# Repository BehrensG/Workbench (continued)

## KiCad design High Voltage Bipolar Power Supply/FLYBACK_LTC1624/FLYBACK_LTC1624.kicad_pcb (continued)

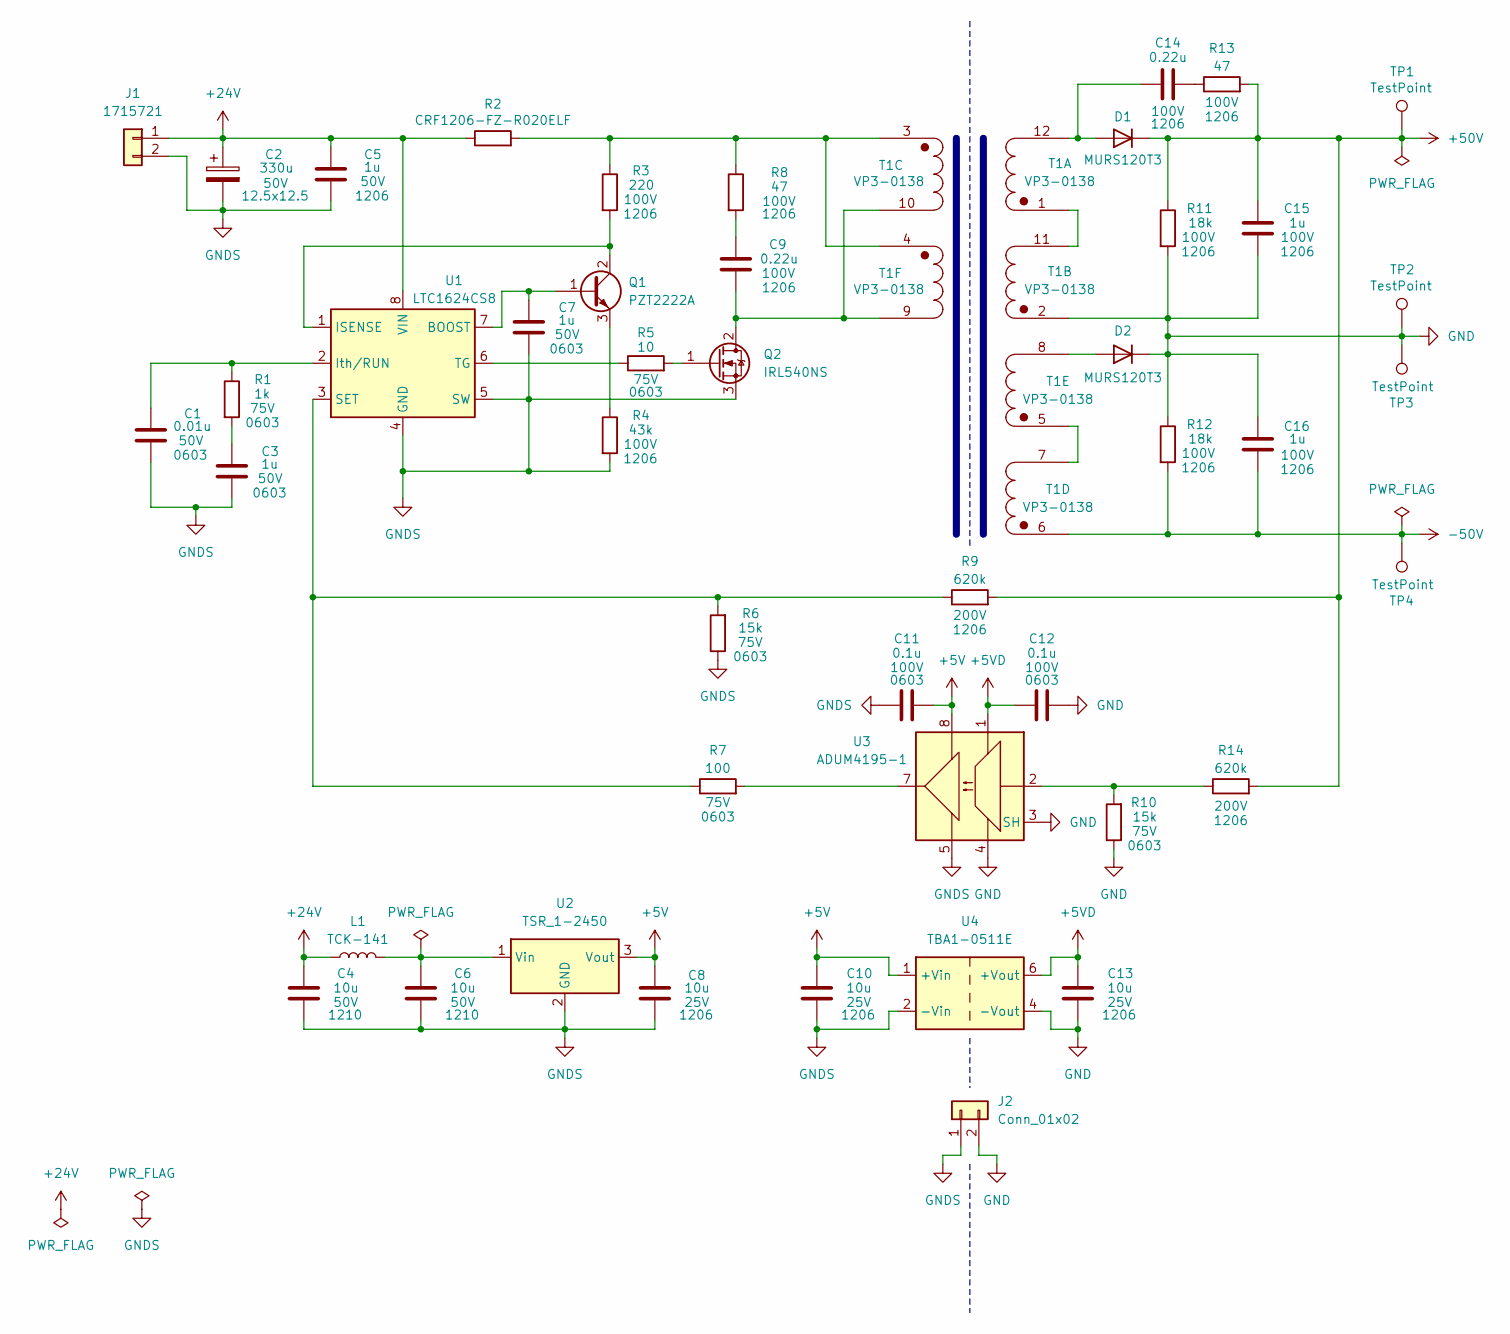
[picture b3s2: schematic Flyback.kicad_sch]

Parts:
C1: 0.01u; C_0603_1608Metric_Pad1.08x0.95mm_HandSolder; Voltage 50V
C2: 330u; CP_Elec_10x10; Voltage 50V
C3, C7: 1u; C_0603_1608Metric_Pad1.08x0.95mm_HandSolder; Voltage 50V
C4, C6: 10u; C_1210_3225Metric_Pad1.33x2.70mm_HandSolder; Voltage 50V
C5: 1u; C_1206_3216Metric_Pad1.33x1.80mm_HandSolder; Voltage 50V
C8, C10, C13: 10u; C_1206_3216Metric_Pad1.33x1.80mm_HandSolder; Voltage 25V
C9, C14: 0.22u; C_1206_3216Metric_Pad1.33x1.80mm_HandSolder; Voltage 100V
C11, C12: 0.1u; C_0603_1608Metric_Pad1.08x0.95mm_HandSolder; Voltage 100V
C15, C16: 1u; C_1206_3216Metric_Pad1.33x1.80mm_HandSolder; Voltage 100V
D1, D2: MURS120T3; D_SMB
J1: 1715721; TerminalBlock_Phoenix_MKDS-1,5-2_1x02_P5.00mm_Horizontal
J2: Conn_01x02; PinHeader_1x02_P2.54mm_Vertical
L1: TCK-141
Q1: PZT2222A; SOT-223-3_TabPin2
Q2: IRL540NS; TO-263-2
R1: 1k; R_0603_1608Metric_Pad0.98x0.95mm_HandSolder; Voltage 75V
R2: CRF1206-FZ-R020ELF; R_1206_3216Metric_Pad1.30x1.75mm_HandSolder
R3: 220; R_1206_3216Metric_Pad1.30x1.75mm_HandSolder; Voltage 100V
R4: 43k; R_1206_3216Metric_Pad1.30x1.75mm_HandSolder; Voltage 100V
R5: 10; R_0603_1608Metric_Pad0.98x0.95mm_HandSolder; Voltage 75V
R6, R10: 15k; R_0603_1608Metric_Pad0.98x0.95mm_HandSolder; Voltage 75V
R7: 100; R_0603_1608Metric_Pad0.98x0.95mm_HandSolder; Voltage 75V
R8, R13: 47; R_1206_3216Metric_Pad1.30x1.75mm_HandSolder; Voltage 100V
R9, R14: 620k; R_1206_3216Metric_Pad1.30x1.75mm_HandSolder; Voltage 200V
R11, R12: 18k; R_1206_3216Metric_Pad1.30x1.75mm_HandSolder; Voltage 100V
T1: VP3-0138; VP3
TP1, TP2, TP3, TP4: TestPoint; TestPoint_THTPad_D3.0mm_Drill1.5mm
U1: LTC1624CS8; SOIC-8_3.9x4.9mm_P1.27mm
U2: TSR_1-2450; Converter_DCDC_TRACO_TSR-1_THT
U3: ADUM4195-1; SSO-8_6.8x5.9mm_P1.27mm_Clearance8mm
U4: TBA1-0511E; Converter_DCDC_TRACO_TBA1-xxxxE_Single_THT

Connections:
+5V: C8.1, C10.1, C11.2, U2.3 (Vout), U3.8, U4.1 (+Vin)
+5VD: C12.1, C13.1, U3.1, U4.6 (+Vout)
+24V: C2.1, C4.1, C5.1, J1.1, L1.1, R2.1, U1.8 (VIN)
+50V: C15.1, D1.1 (K), R9.2, R11.1, R13.2, R14.2, TP1.1; also elsewhere on the board
-50V: C16.2, R12.2, T1.6, TP4.1; also elsewhere on the board
GND: C12.2, C13.2, C15.2, C16.1, D2.1 (K), J2.2, R10.1, R11.2, R12.1, T1.2, TP2.1, TP3.1, U3.3 (SH), U3.4, U4.4 (-Vout); also elsewhere on the board
GNDS: C1.2, C2.2, C3.2, C4.2, C5.2, C6.2, C7.2, C8.2, C10.2, C11.1, J1.2, J2.1, Q2.3 (S), R4.2, R6.1, U1.4 (GND), U1.5 (SW), U2.2 (GND), U3.5, U4.2 (-Vin)
unnamed: C3.1, R1.2
unnamed: C9.1, R8.2
unnamed: C14.2, R13.1
unnamed: C14.1, D1.2 (A), T1.12
unnamed: D2.2 (A), T1.8
unnamed: C7.1, Q1.1 (B), U1.7 (BOOST)
unnamed: Q1.2 (C), R3.2, U1.1 (ISENSE)
unnamed: Q1.3 (E), R4.1
unnamed: C9.2, Q2.2 (D), T1.9, T1.10
unnamed: Q2.1 (G), R5.2
unnamed: R2.2, R3.1, R8.1, T1.3, T1.4
unnamed: R7.2, U3.7
unnamed: R10.2, R14.1, U3.2
unnamed: T1.1, T1.11
unnamed: T1.5, T1.7
unnamed: C1.1, R1.1, U1.2 (Ith/RUN)
unnamed: R6.2, R7.1, R9.1, U1.3 (SET)
unnamed: R5.1, U1.6 (TG)
unnamed: C6.1, L1.2, U2.1 (Vin)

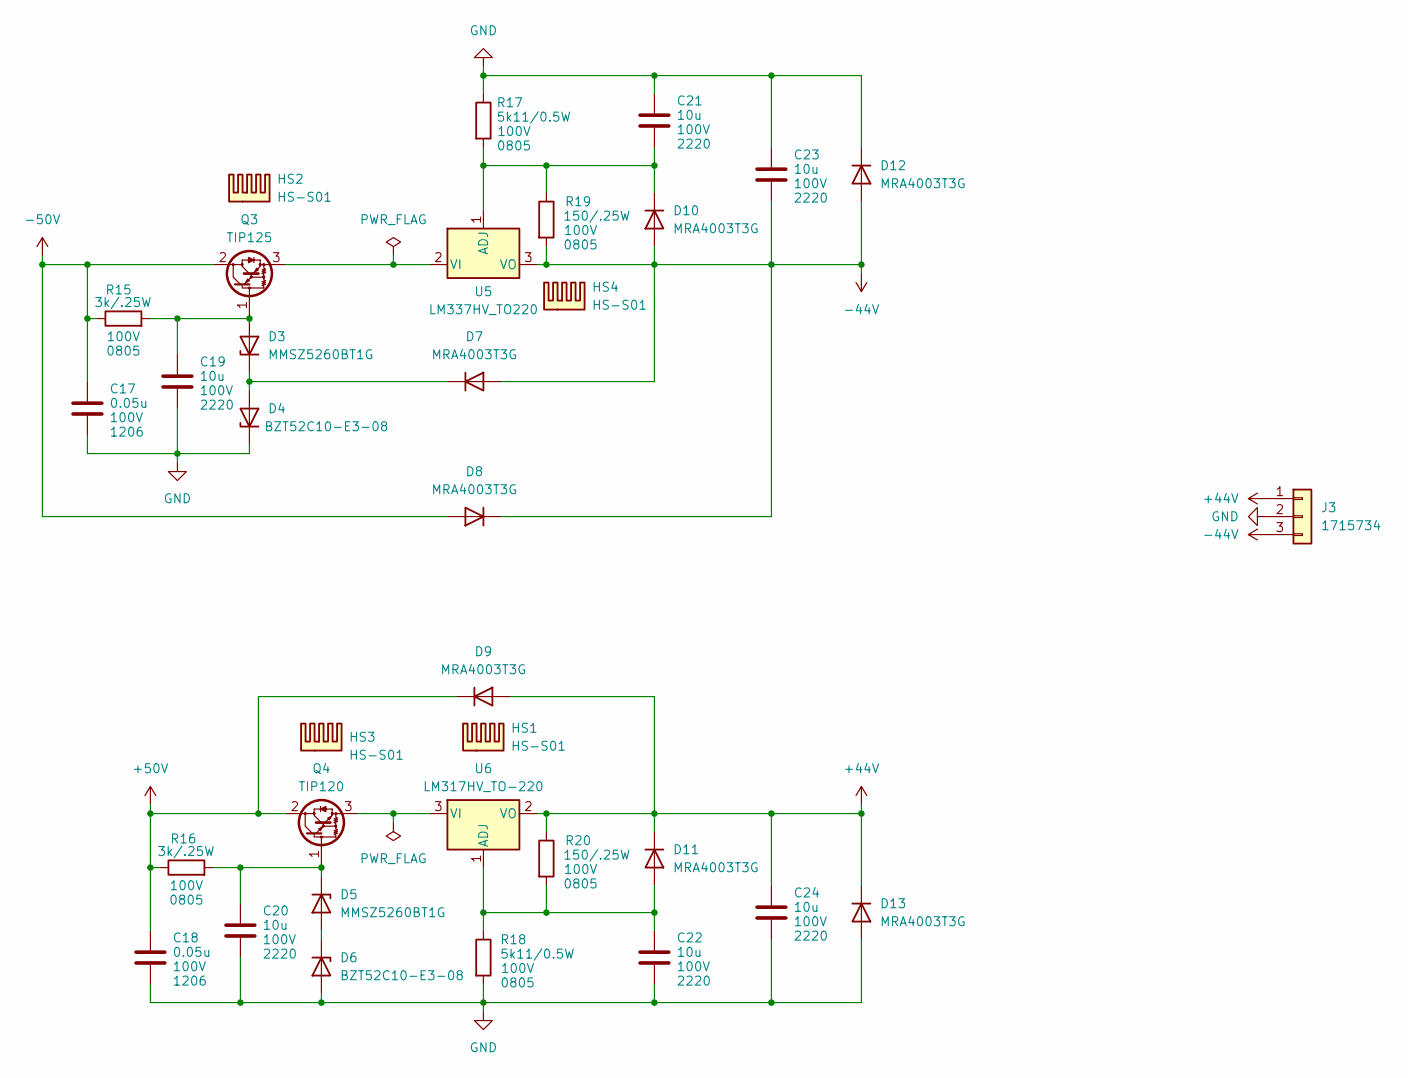
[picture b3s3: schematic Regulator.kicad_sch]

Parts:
C17, C18: 0.05u; C_1206_3216Metric_Pad1.33x1.80mm_HandSolder; Voltage 100V
C19, C20, C21, C22, C23, C24: 10u; C_2220_5750Metric_Pad1.97x5.40mm_HandSolder; Voltage 100V
D3, D5: MMSZ5260BT1G; D_SOD-123
D4, D6: BZT52C10-E3-08; D_SOD-123
D7, D8, D9, D10, D11, D12, D13: MRA4003T3G; D_SMA
HS1, HS2, HS3, HS4: HS-S01; Heatsink_Stonecold_HS-S01_13.21x6.35mm
J3: 1715734; TerminalBlock_Phoenix_MKDS-1,5-3-5.08_1x03_P5.08mm_Horizont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
Q3: TIP125; TO-220-3_Vertical
Q4: TIP120; TO-220-3_Vertical
R15, R16: 3k/.25W; R_0805_2012Metric_Pad1.20x1.40mm_HandSolder; Voltage 100V
R17, R18: 5k11/0.5W; R_0805_2012Metric_Pad1.20x1.40mm_HandSolder; Voltage 100V
R19, R20: 150/.25W; R_0805_2012Metric_Pad1.20x1.40mm_HandSolder; Voltage 100V
U5: LM337HV_TO220; TO-220-3_Vertical
U6: LM317HV_TO-220; TO-220-3_Vertical

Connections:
+44V: C24.1, D9.2 (A), D11.1 (K), D13.1 (K), J3.1, R20.1, U6.2 (VO)
+50V: C18.1, D9.1 (K), Q4.2 (C), R16.1; also elsewhere on the board
-44V: C23.2, D7.2 (A), D8.1 (K), D10.2 (A), D12.2 (A), J3.3, R19.2, U5.3 (VO)
-50V: C17.1, D8.2 (A), Q3.2 (C), R15.1; also elsewhere on the board
GND: C17.2, C18.2, C19.2, C20.2, C21.1, C22.2, C23.1, C24.2, D4.1 (K), D6.2 (A), D12.1 (K), D13.2 (A), J3.2, R17.1, R18.2; also elsewhere on the board
unnamed: C19.1, D3.2 (A), Q3.1 (B), R15.2
unnamed: D3.1 (K), D4.2 (A), D7.1 (K)
unnamed: D5.2 (A), D6.1 (K)
unnamed: C20.1, D5.1 (K), Q4.1 (B), R16.2
unnamed: C21.2, D10.1 (K), R17.2, R19.1, U5.1 (ADJ)
unnamed: C22.1, D11.2 (A), R18.1, R20.2, U6.1 (ADJ)
unnamed: Q3.3 (E), U5.2 (VI)
unnamed: Q4.3 (E), U6.3 (VI)

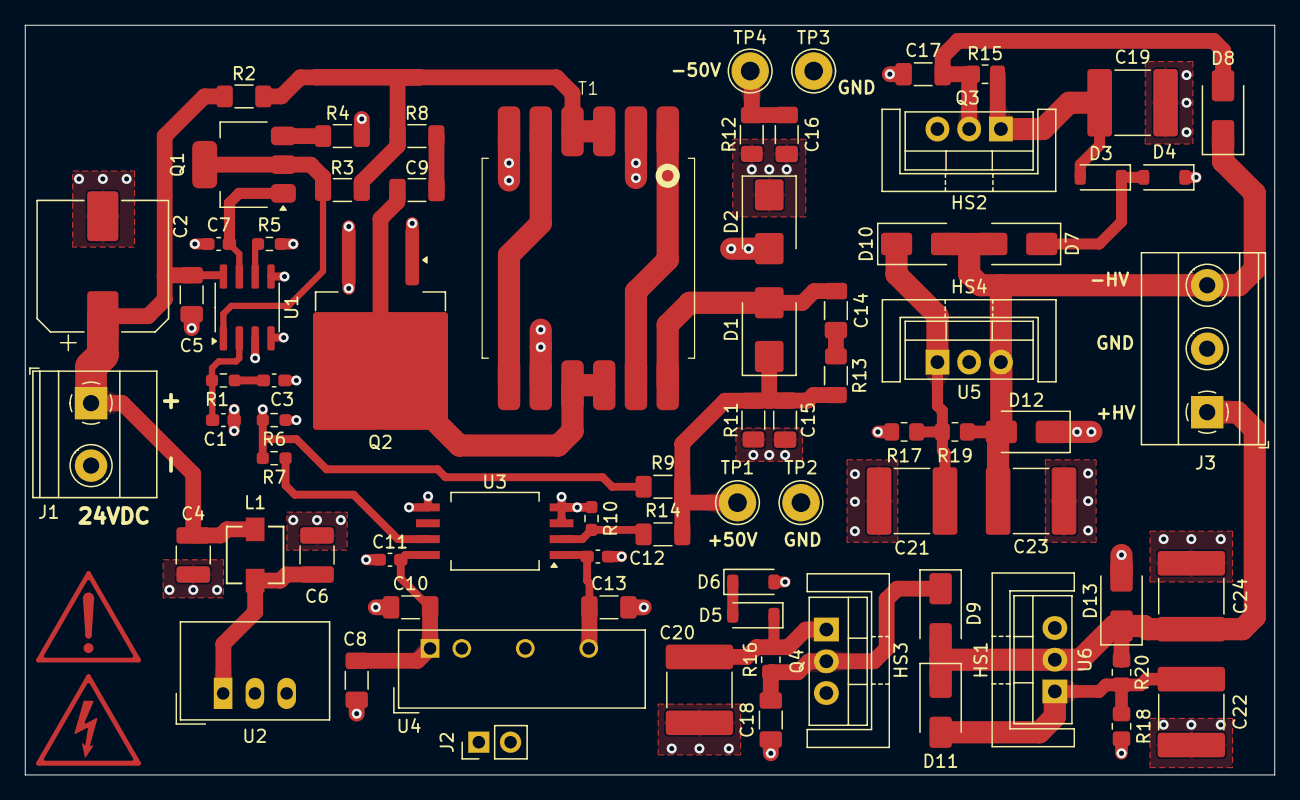
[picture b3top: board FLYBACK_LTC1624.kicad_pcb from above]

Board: 4 copper layers, 100.0 x 60.0 mm, 82 parts (0 on the bottom side), 36 nets.

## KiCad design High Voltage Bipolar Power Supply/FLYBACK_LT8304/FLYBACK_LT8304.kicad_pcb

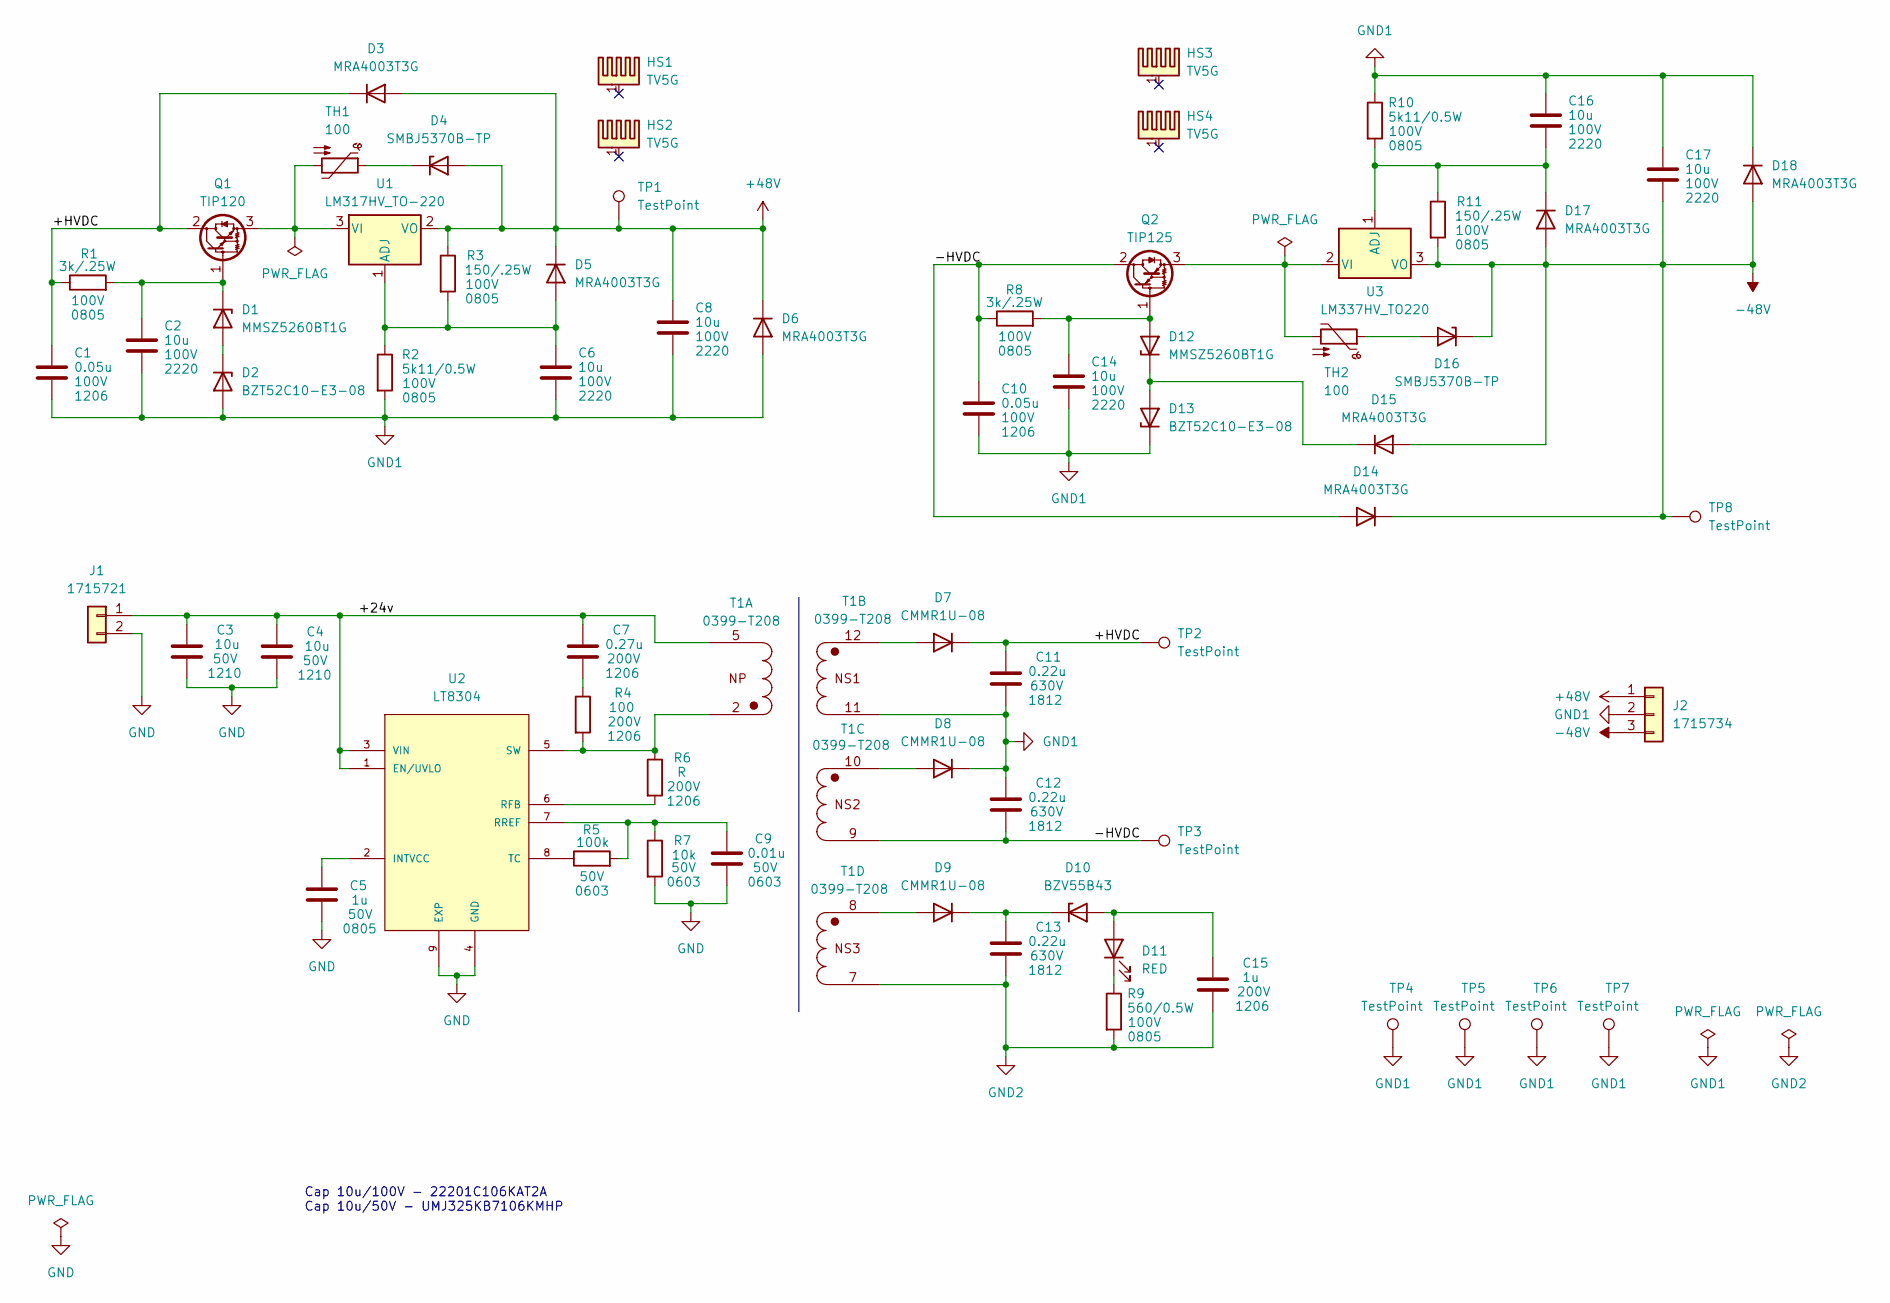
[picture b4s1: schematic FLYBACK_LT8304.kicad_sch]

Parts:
C1, C10: 0.05u; C_1206_3216Metric_Pad1.33x1.80mm_HandSolder; Voltage 100V
C2, C6, C8, C14, C16, C17: 10u; C_2220_5750Metric_Pad1.97x5.40mm_HandSolder; Voltage 100V
C3, C4: 10u; C_1210_3225Metric_Pad1.33x2.70mm_HandSolder; Voltage 50V
C5: 1u; C_0805_2012Metric_Pad1.18x1.45mm_HandSolder; Voltage 50V
C7: 0.27u; C_1206_3216Metric_Pad1.33x1.80mm_HandSolder; Voltage 200V
C9: 0.01u; C_0603_1608Metric_Pad1.08x0.95mm_HandSolder; Voltage 50V
C11, C12, C13: 0.22u; C_1812_4532Metric_Pad1.57x3.40mm_HandSolder; Voltage 630V
C15: 1u; C_1206_3216Metric_Pad1.33x1.80mm_HandSolder; Voltage 200V
D1, D12: MMSZ5260BT1G; D_SOD-123
D2, D13: BZT52C10-E3-08; D_SOD-123
D3, D5, D6, D14, D15, D17, D18: MRA4003T3G; D_SMA
D4, D16: SMBJ5370B-TP; D_SMB
D7, D8, D9: CMMR1U-08; D_SOD-123F
D10: BZV55B43; D_MiniMELF
D11: RED; LED_0603_1608Metric_Pad1.05x0.95mm_HandSolder
HS1, HS2, HS3, HS4: TV5G; Heatsink_AAVID_TV5G_TO220_Horizontal
J1: 1715721; TerminalBlock_Phoenix_MKDS-1,5-2_1x02_P5.00mm_Horizontal
J2: 1715734; TerminalBlock_Phoenix_MKDS-1,5-3-5.08_1x03_P5.08mm_Horizont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
Q1: TIP120; TO-220-3_Horizontal_TabDown
Q2: TIP125; TO-220-3_Horizontal_TabDown
R1, R8: 3k/.25W; R_0805_2012Metric_Pad1.20x1.40mm_HandSolder; Voltage 100V
R2, R10: 5k11/0.5W; R_0805_2012Metric_Pad1.20x1.40mm_HandSolder; Voltage 100V
R3, R11: 150/.25W; R_0805_2012Metric_Pad1.20x1.40mm_HandSolder; Voltage 100V
R4: 100; R_1206_3216Metric_Pad1.30x1.75mm_HandSolder; Voltage 200V
R5: 100k; R_0603_1608Metric_Pad0.98x0.95mm_HandSolder; Voltage 50V
R6: R; R_1206_3216Metric_Pad1.30x1.75mm_HandSolder; Voltage 200V
R7: 10k; R_0603_1608Metric_Pad0.98x0.95mm_HandSolder; Voltage 50V
R9: 560/0.5W; R_0805_2012Metric_Pad1.20x1.40mm_HandSolder; Voltage 100V
T1: 0399-T208
TH1, TH2: 100
TP1, TP2, TP3, TP4, TP5, TP6, TP7, TP8: TestPoint; TestPoint_THTPad_D3.0mm_Drill1.5mm
U1: LM317HV_TO-220; TO-220-3_Horizontal_TabDown
U2: LT8304; SOIC-8-1EP_3.9x4.9mm_P1.27mm_EP2.29x3mm_ThermalVias; PARTREV LT0217_REV_A
U3: LM337HV_TO220; TO-220-3_Horizontal_TabDown

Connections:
+48V: C8.1, D3.2 (A), D4.2 (A), D5.1 (K), D6.1 (K), J2.1, R3.1, TP1.1, U1.2 (VO)
-48V: C17.2, D14.1 (K), D15.2 (A), D16.1 (K), D17.2 (A), D18.2 (A), J2.3, R11.2, TP8.1, U3.3 (VO)
/+24v: C3.1, C4.1, C7.1, J1.1, T1.5, U2.1 (EN/UVLO), U2.3 (VIN)
/+HVDC: C1.1, C11.1, D3.1 (K), D7.1 (K), Q1.2 (C), R1.1, TP2.1
/-HVDC: C10.1, C12.2, D14.2 (A), Q2.2 (C), R8.1, T1.9, TP3.1
GND: C3.2, C4.2, C5.2, C9.2, J1.2, R7.2, U2.4 (GND), U2.9 (EXP)
GND1: C1.2, C2.2, C6.2, C8.2, C10.2, C11.2, C12.1, C14.2, C16.1, C17.1, D2.2 (A), D6.2 (A), D8.1 (K), D13.1 (K), D18.1 (K), J2.2, R2.2, R10.1, T1.11, TP4.1, TP5.1, TP6.1, TP7.1
GND2: C13.2, C15.2, R9.2, T1.7
unnamed: C7.2, R4.1
unnamed: D1.2 (A), D2.1 (K)
unnamed: C2.1, D1.1 (K), Q1.1 (B), R1.2
unnamed: D4.1 (K), TH1.1
unnamed: C6.1, D5.2 (A), R2.1, R3.2, U1.1 (ADJ)
unnamed: D7.2 (A), T1.12
unnamed: D8.2 (A), T1.10
unnamed: D9.2 (A), T1.8
unnamed: C15.1, D10.2 (A), D11.2 (A)
unnamed: C13.1, D9.1 (K), D10.1 (K)
unnamed: D11.1 (K), R9.1
unnamed: C14.1, D12.2 (A), Q2.1 (B), R8.2
unnamed: D12.1 (K), D13.2 (A), D15.1 (K)
unnamed: D16.2 (A), TH2.1
unnamed: C16.2, D17.1 (K), R10.2, R11.1, U3.1 (ADJ)
unnamed: Q1.3 (E), TH1.2, U1.3 (VI)
unnamed: Q2.3 (E), TH2.2, U3.2 (VI)
unnamed: C5.1, U2.2 (INTVCC)
unnamed: R6.2, U2.6 (RFB)
unnamed: C9.1, R5.2, R7.1, U2.7 (RREF)
unnamed: R4.2, R6.1, T1.2, U2.5 (SW)
unnamed: R5.1, U2.8 (TC)

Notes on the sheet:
Cap 10u/100V - 22201C106KAT2A Cap 10u/50V - UMJ325KB7106KMHP

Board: 2 copper layers, 65 parts (0 on the bottom side), 25 nets, no tracks yet.

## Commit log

2024-11-19 Init
2024-11-20 Simulations
2024-11-20 FLYBACK_LT8304: Schematic design
2024-11-21 FLYBACK_LTC1624 : Schematic desing
2024-11-23 FLYBACK_LTC1624: PCB layout
2024-11-24 FLYBACK_LTC1624 : Design failed, can't buy LM377HV for -50V
2024-11-24 Cleanup
2024-11-25 UCC25800 : Schematic design
2024-11-26 UCC25800 : Changes in sch and assignment of footprints.
2024-11-26 UCC25800 : PCB layout
2024-12-01 BOOST_LT8365 : Design for bipolar 110V supply
2024-12-02 Deleted LM317 and LM337 regulator circuits because of current lost on the volateges setup resistors.
2024-12-04 BOOST_LT8365 : PCB layout
2024-12-07 BOOST_LT8365 : PCB design done
